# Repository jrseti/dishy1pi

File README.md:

# dishy1pi
Satellite dish motor control for Raspberry Pi, hardware and software

This project was developed in Windows 11 with Python 3.12.

## Prerequisites

It is suggested to create a Python3 virtual environment for this project. Here is how:

- From the project root directory "python3 -m venv .venv"
- .\.venv\Scripts\activate (Note: this command will be a bit different on Linux or MacOS)

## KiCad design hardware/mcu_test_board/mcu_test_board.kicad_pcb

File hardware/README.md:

# Hardware Projects for Dishy1Pi

This directory contains hardware projects and designs related to the Dishy1Pi, a Raspberry Pi Hat tocontrol motors and encoders for a satellite dish.

## Projects

- **Dishy1Pi**: The main project, a Raspberry Pi Hat designed to control motors and encoders for a satellite dish. It includes schematics, PCB layouts, and bill of materials (BOM).

- **power-supply**: A project focused on designing a power supply unit for the Dishy1Pi, ensuring it can provide the necessary voltage and current for operation.

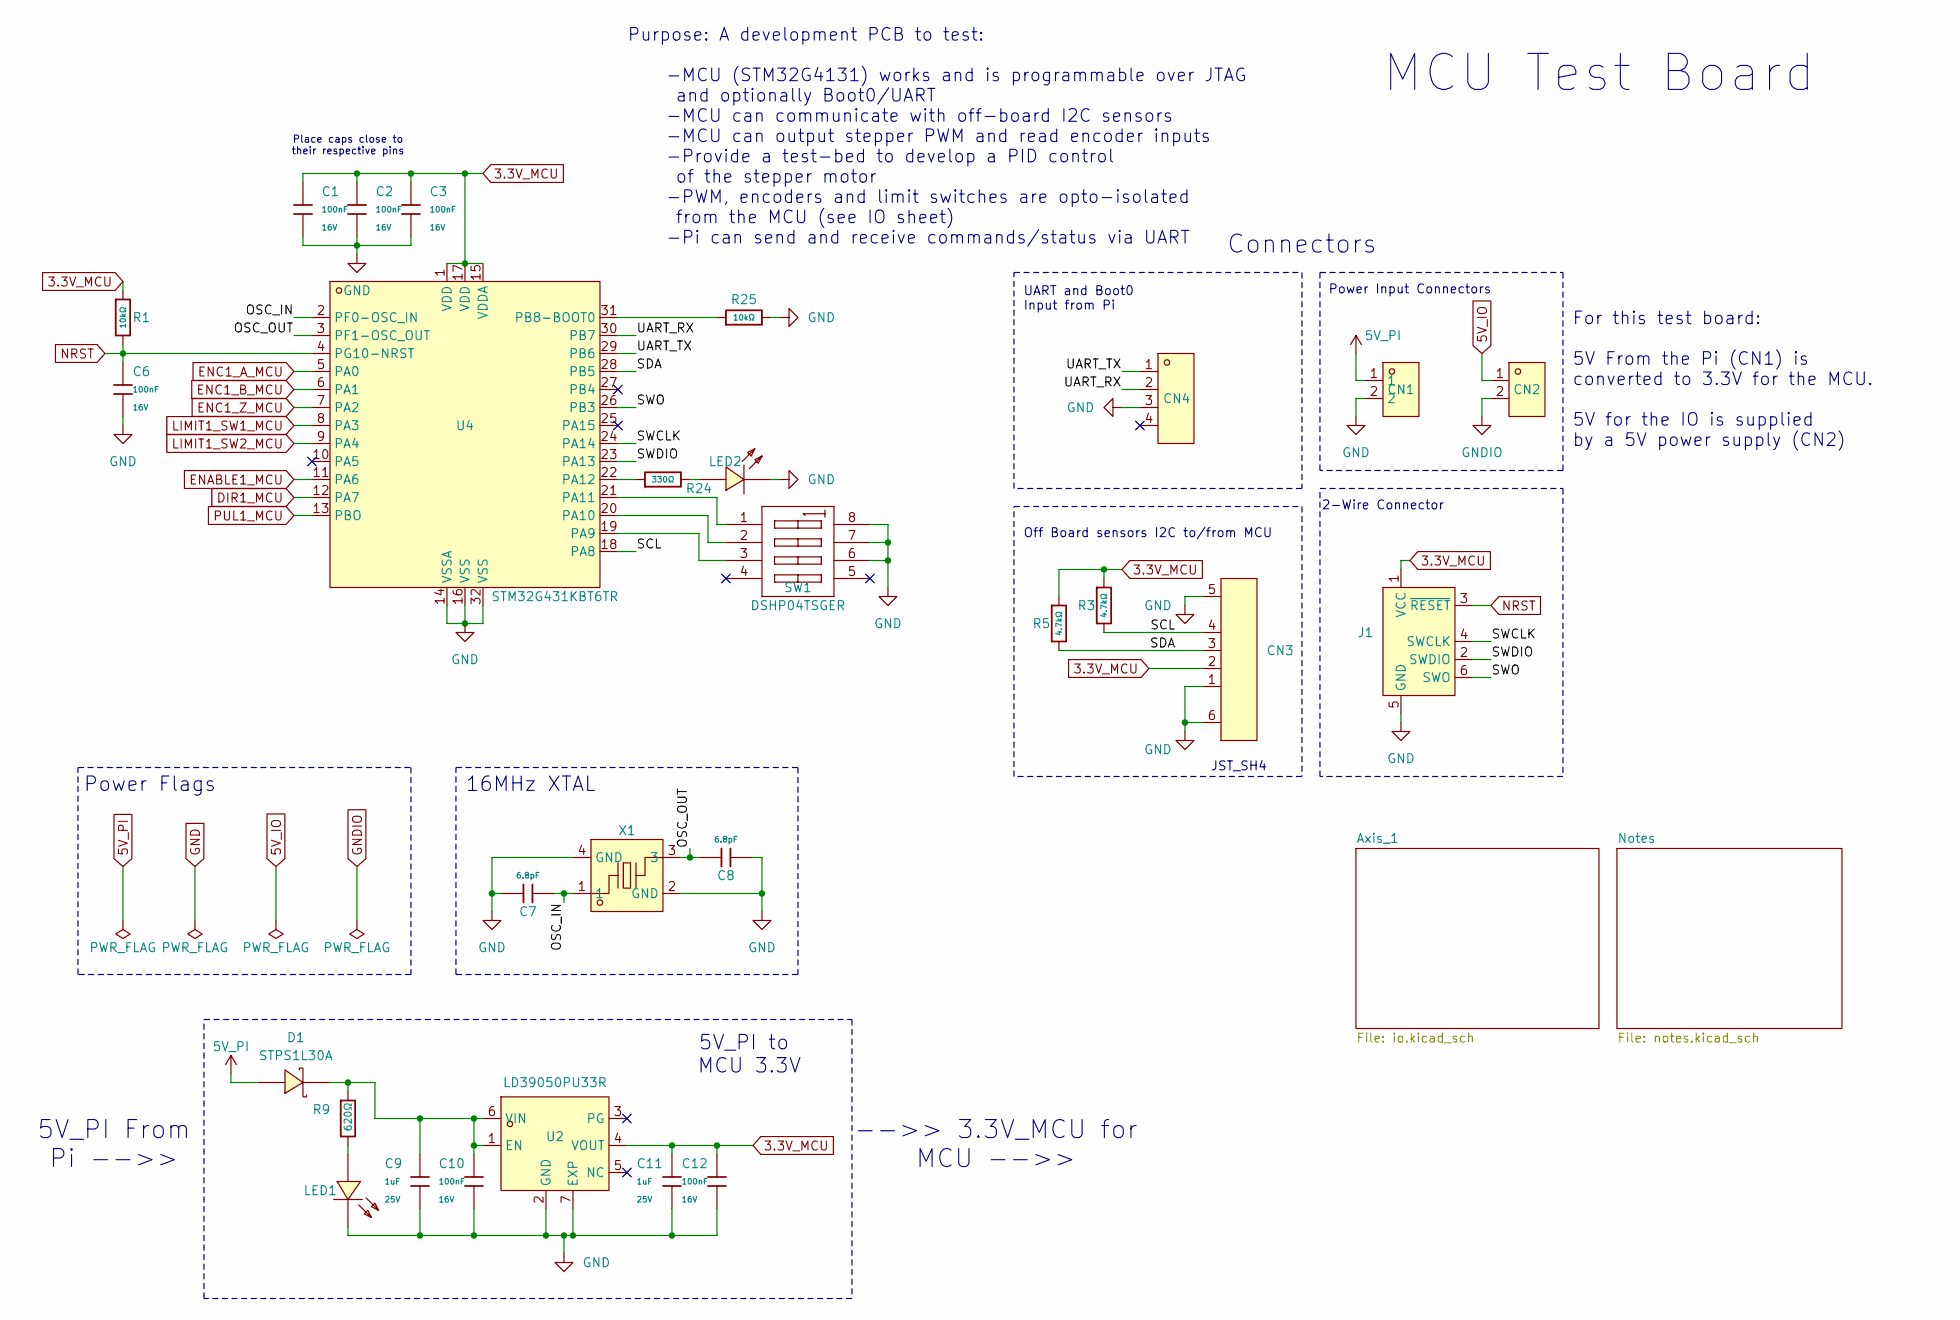
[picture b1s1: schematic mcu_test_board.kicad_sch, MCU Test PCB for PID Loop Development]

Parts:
C1, C2, C3, C6, C10, C12: 100nF; C_0402; Voltage Rated 16V; Tolerance ±10%; Part CL05B104KO5NNNC; LCSC C1525
C7, C8: 6.8pF; C_0402; Voltage Rated 50V; Part 0402CG6R8C500NT; LCSC C1576
C9, C11: 1uF; C_0402; Voltage Rated 25V; Tolerance ±10%; Part CL05A105KA5NQNC; LCSC C52923
CN1, CN2: KF2EDGR-2.54-2P; CONN-TH_P2.54_KF2EDGR-2.54-2P; LCSC Part C577594
CN3: SM04B-SRSS-TB (LF)(SN); CONN-SMD_4P-P1.00_SM04B-SRSS-TB-LF-SN; LCSC Part C160404
CN4: KF2EDGR-2.54-4P; CONN-TH_4P-P2.54_KF2EDGR-2.54-4P; LCSC Part C577596
D1: STPS1L30A; SMA_L4.3-W2.6-LS5.2-RD; LCSC Part C157388
J1: Conn_ARM_SWD_TagConnect_TC2030-NL; Tag-Connect_TC2030-IDC-NL_2x03_P1.27mm_Vertical
LED1, LED2: 19-213SYGC/S530-E2/TR8; LED-SMD_L1.6-W0.8-FD_GREEN; LCSC Part C409444
R1, R25: 10kΩ; R_0402; Overload Voltage (Max) 50V; Tolerance ±1%; Part 0402WGF1002TCE; LCSC C25744
R3, R5: 4.7kΩ; R_0402; Overload Voltage (Max) 50V; Tolerance ±1%; Part 0402WGF4701TCE; LCSC C25900
R9: 620Ω; R_0603; Overload Voltage (Max) 75V; Tolerance ±1%; Part 0603WAF6200T5E; LCSC C23220
R24: 330Ω; R_0402; Overload Voltage (Max) 50V; Tolerance ±1%; Part 0402WGF3300TCE; LCSC C25104
SW1: DSHP04TSGER; SW-SMD_8P-L6.7-W5.4-P1.27-LS8.4; LCSC Part C40736
U2: LD39050PU33R; DFN-6_L3.0-W3.0-P0.95-LS3.1-TL-EP; LCSC Part C132827
U4: STM32G431KBT6TR; LQFP-32_L7.0-W7.0-P0.80-LS9.0-BL; LCSC Part C5270317
X1: NX2016SA-16MHZ-EXS00A-CS07826; CRYSTAL-SMD_4P-L2.0-W1.6-BL; LCSC Part C7322371

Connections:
3.3V_MCU: C1.1, C2.1, C3.1, C11.1, C12.1, CN3.2, J1.1 (VCC), R1.1, R3.1, R5.1, U2.4 (VOUT), U4.1 (VDD), U4.15 (VDDA), U4.17 (VDD); also elsewhere on the board
5V_IO: CN2.1; also elsewhere on the board
5V_PI: CN1.1, D1.2 (A)
/OSC_IN: C7.2, U4.2 (PF0-OSC_IN), X1.1
/OSC_OUT: C8.1, U4.3 (PF1-OSC_OUT), X1.3
/SCL: CN3.4, R3.2, U4.18 (PA8)
/SDA: CN3.3, R5.2, U4.28 (PB5)
/SWCLK: J1.4 (SWCLK), U4.24 (PA14)
/SWDIO: J1.2 (SWDIO), U4.23 (PA13)
/SWO: J1.6 (SWO), U4.26 (PB3)
/UART_RX: CN4.2, U4.30 (PB7)
/UART_TX: CN4.1, U4.29 (PB6)
DIR1_MCU: U4.12 (PA7); also elsewhere on the board
ENABLE1_MCU: U4.11 (PA6); also elsewhere on the board
ENC1_A_MCU: U4.5 (PA0); also elsewhere on the board
ENC1_B_MCU: U4.6 (PA1); also elsewhere on the board
ENC1_Z_MCU: U4.7 (PA2); also elsewhere on the board
GND: C1.2, C2.2, C3.2, C6.2, C7.1, C8.2, C9.2, C10.2, C11.2, C12.2, CN1.2, CN3.1, CN3.5, CN3.6, CN4.3, J1.5 (GND), LED1.2 (-), LED2.2 (-), R25.2, SW1.6 (B3), SW1.7 (B2), SW1.8 (B1), U2.2 (GND), U2.7 (EXP), U4.14 (VSSA), U4.16 (VSS), U4.32 (VSS), X1.2 (GND), X1.4 (GND); also elsewhere on the board
GNDIO: CN2.2; also elsewhere on the board
LIMIT1_SW1_MCU: U4.8 (PA3); also elsewhere on the board
LIMIT1_SW2_MCU: U4.9 (PA4); also elsewhere on the board
NRST: C6.1, J1.3 (~RESET), R1.2, U4.4 (PG10-NRST)
unnamed: C9.1, C10.1, D1.1 (C), R9.1, U2.1 (EN), U2.6 (VIN)
unnamed: LED1.1 (+), R9.2
unnamed: LED2.1 (+), R24.2
unnamed: SW1.1 (A1), U4.21 (PA11)
unnamed: SW1.2 (A2), U4.20 (PA10)
unnamed: SW1.3 (A3), U4.19 (PA9)
unnamed: R24.1, U4.22 (PA12)
unnamed: R25.1, U4.31 (PB8-BOOT0)
PUL1_MCU: U4.13 (PBO); also elsewhere on the board

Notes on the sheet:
2-Wire Connector
16MHz XTAL
Off Board sensors I2C to/from MCU
Connectors
JST_SH4
Power Input Connectors
UART and Boot0 Input from Pi
For this test board: 5V From the Pi (CN1) is converted to 3.3V for the MCU. 5V for the IO is supplied by a 5V power supply (CN2)
Place caps close to their respective pins
Power Flags
-->> 3.3V_MCU for MCU -->>
MCU Test Board
Purpose: A development PCB to test: -MCU (STM32G4131) works and is programmable over JTAG and optionally Boot0/UART -MCU can communicate with off-board I2C sensors -MCU can output stepper PWM and read encoder inputs -Provide a test-bed to develop a PID control of the stepper motor -PWM, encoders an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
5V_PI to MCU 3.3V
5V_PI From Pi -->>

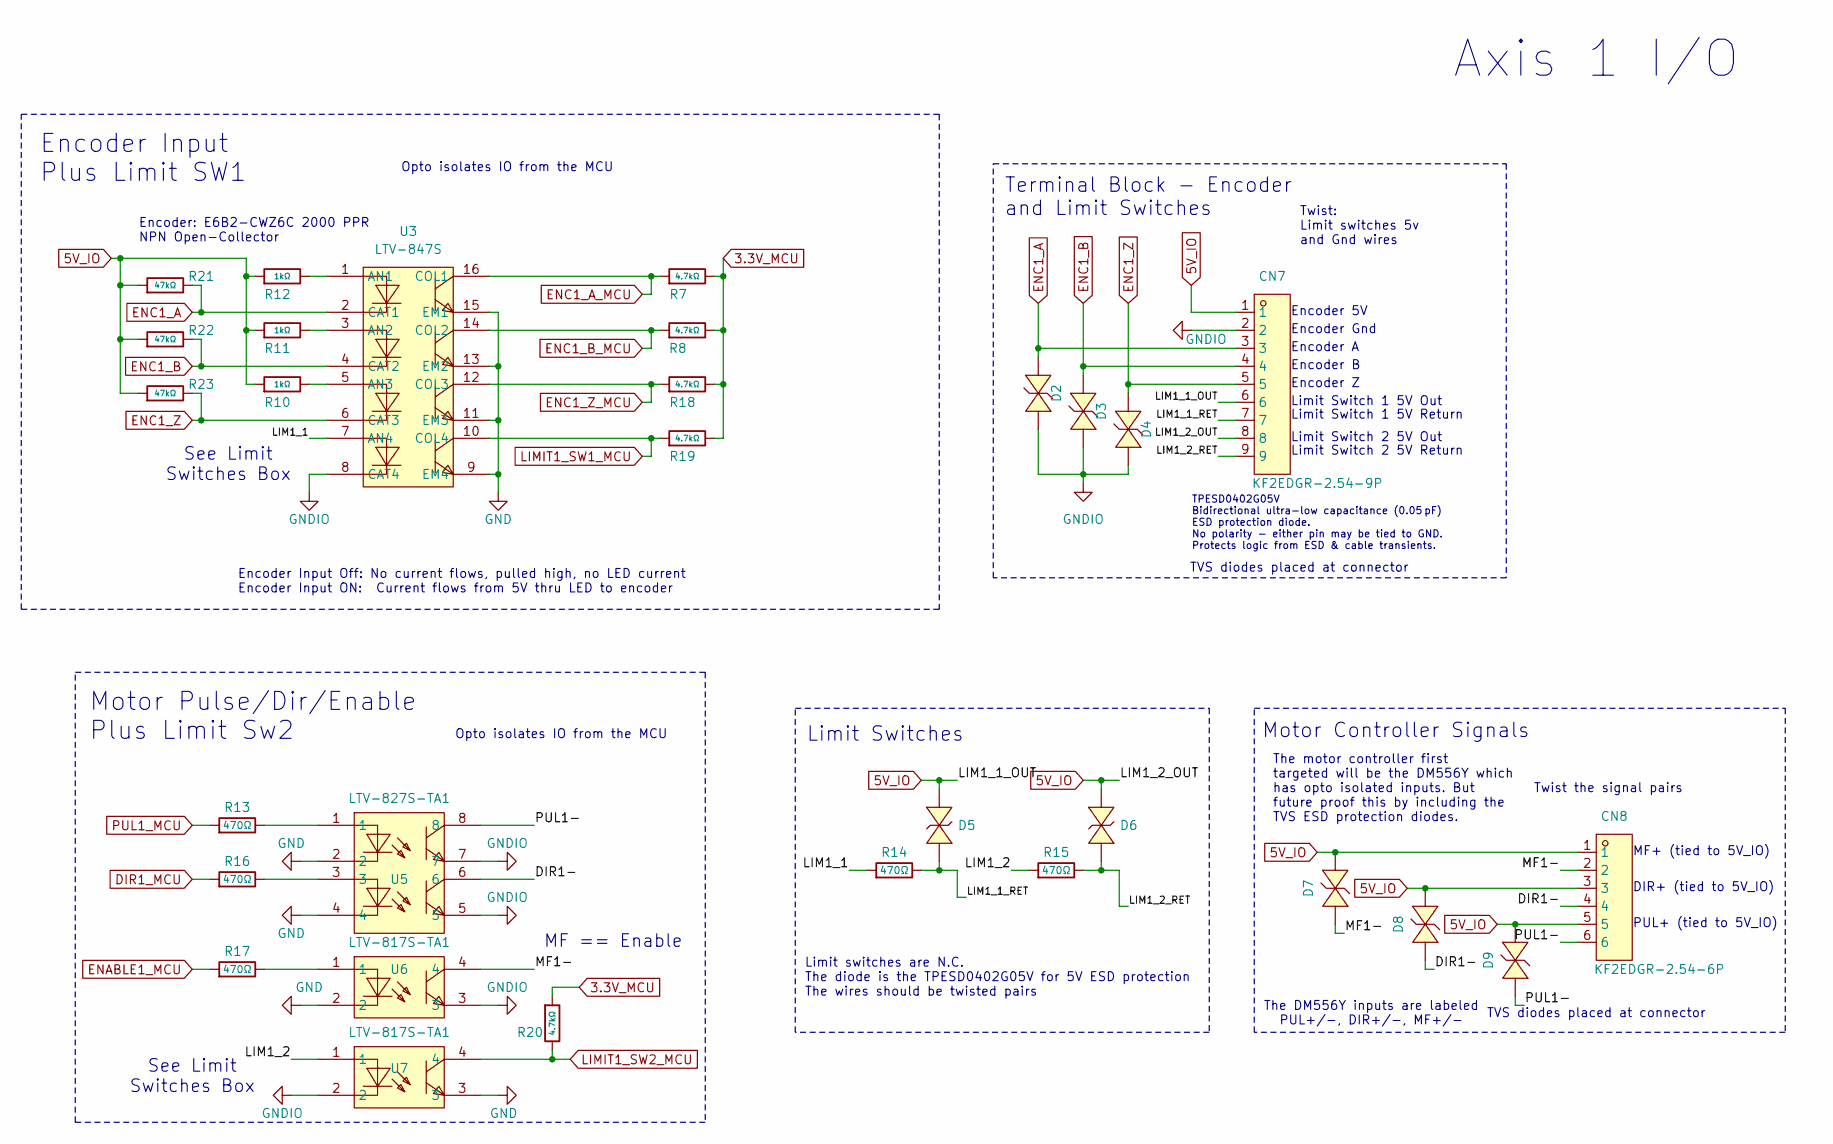
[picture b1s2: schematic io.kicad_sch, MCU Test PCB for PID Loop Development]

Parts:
CN7: KF2EDGR-2.54-9P; CONN-TH_9P-P2.54_KF2EDGR-2.54-9P; LCSC Part C577601
CN8: KF2EDGR-2.54-6P; CONN-TH_KF2EDGR-2.54-6P; LCSC Part C577598
D2, D3, D4, D7, D8, D9: TPESD0402G05V; D0402-BI; LCSC Part C558615
D5, D6: TPESD0402G05V; D0402-BI; LCSC Part C558617
R7, R8, R18, R19, R20: 4.7kΩ; R_0603; Overload Voltage (Max) 75V; Tolerance ±1%; Part 0603WAF4701T5E; LCSC C23162
R10, R11, R12: 1kΩ; R_0402; Overload Voltage (Max) 50V; Tolerance ±1%; Part 0402WGF1001TCE; LCSC C11702
R13, R14, R15, R16, R17: 470Ω; R_0402; Overload Voltage (Max) 50V; Tolerance ±1%; Part 0402WGF4700TCE; LCSC C25117
R21, R22, R23: 47kΩ; R_0402; Overload Voltage (Max) 50V; Tolerance ±1%; Part 0402WGF4702TCE; LCSC C25792
U3: LTV-847S; SMD-16_L20.0-W6.5-P2.54-LS10.2-BL; LCSC Part C114599
U5: LTV-827S-TA1; LTV827S-TA1; LCSC Part C22112
U6, U7: LTV-817S-TA1; LTV817S; LCSC Part C125121

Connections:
3.3V_MCU: R7.2, R8.2, R18.2, R19.2, R20.1; also elsewhere on the board
5V_IO: CN7.1, CN7.6, CN7.8, CN8.1, CN8.3, CN8.5, D5.1, D6.1, D7.1 (K), D8.1 (K), D9.1 (K), R10.1, R11.1, R12.1, R21.1, R22.1, R23.1; also elsewhere on the board
/Axis_1/DIR1-: CN8.4, D8.2 (A), U5.6
/Axis_1/LIM1_1: R14.1, U3.7 (AN4)
/Axis_1/LIM1_1_RET: CN7.7, D5.2, R14.2
/Axis_1/LIM1_2: R15.1, U7.1
/Axis_1/LIM1_2_RET: CN7.9, D6.2, R15.2
/Axis_1/MF1-: CN8.2, D7.2 (A), U6.4
/Axis_1/PUL1-: CN8.6, D9.2 (A), U5.8
DIR1_MCU: R16.1; also elsewhere on the board
ENABLE1_MCU: R17.1; also elsewhere on the board
ENC1_A: CN7.3, D2.1 (K), R21.2, U3.2 (CAT1)
ENC1_A_MCU: R7.1, U3.16 (COL1); also elsewhere on the board
ENC1_B: CN7.4, D3.1 (K), R22.2, U3.4 (CAT2)
ENC1_B_MCU: R8.1, U3.14 (COL2); also elsewhere on the board
ENC1_Z: CN7.5, D4.1 (K), R23.2, U3.6 (CAT3)
ENC1_Z_MCU: R18.1, U3.12 (COL3); also elsewhere on the board
GND: U3.9 (EM4), U3.11 (EM3), U3.13 (EM2), U3.15 (EM1), U5.2, U5.4, U6.2, U7.3; also elsewhere on the board
GNDIO: CN7.2, D2.2 (A), D3.2 (A), D4.2 (A), U3.8 (CAT4), U5.5, U5.7, U6.3, U7.2; also elsewhere on the board
LIMIT1_SW1_MCU: R19.1, U3.10 (COL4); also elsewhere on the board
LIMIT1_SW2_MCU: R20.2, U7.4; also elsewhere on the board
unnamed: R13.2, U5.1
unnamed: R16.2, U5.3
unnamed: R17.2, U6.1
unnamed: R12.2, U3.1 (AN1)
unnamed: R11.2, U3.3 (AN2)
unnamed: R10.2, U3.5 (AN3)
PUL1_MCU: R13.1; also elsewhere on the board

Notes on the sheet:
Limit Switch 2 5V Return
Encoder A
Limit switches are N.C. The diode is the TPESD0402G05V for 5V ESD protection The wires should be twisted pairs
PUL+ (tied to 5V_IO)
Opto isolates IO from the MCU
Encoder 5V
Motor Pulse/Dir/Enable Plus Limit Sw2
See Limit Switches Box
Encoder: E6B2-CWZ6C 2000 PPR NPN Open-Collector
Opto isolates IO from the MCU
Encoder Gnd
Axis 1 I/O
Twist: Limit switches 5v and Gnd wires
TPESD0402G05V Bidirectional ultra-low capacitance (0.05 pF) ESD protection diode. No polarity - either pin may be tied to GND. Protects logic from ESD & cable transients.
Limit Switch 2 5V Out
Encoder Input Off: No current flows, pulled high, no LED current Encoder Input ON: Current flows from 5V thru LED to encoder
TVS diodes placed at connector
MF+ (tied to 5V_IO)
Limit Switch 1 5V Return
Terminal Block - Encoder and Limit Switches
The DM556Y inputs are labeled PUL+/-, DIR+/-, MF+/-
Encoder Input Plus Limit SW1
Limit Switches
Motor Controller Signals
Encoder Z
DIR+ (tied to 5V_IO)
The motor controller first targeted will be the DM556Y which has opto isolated inputs. But future proof this by including the TVS ESD protection diodes.
Twist the signal pairs
MF == Enable
Limit Switch 1 5V Out
Encoder B

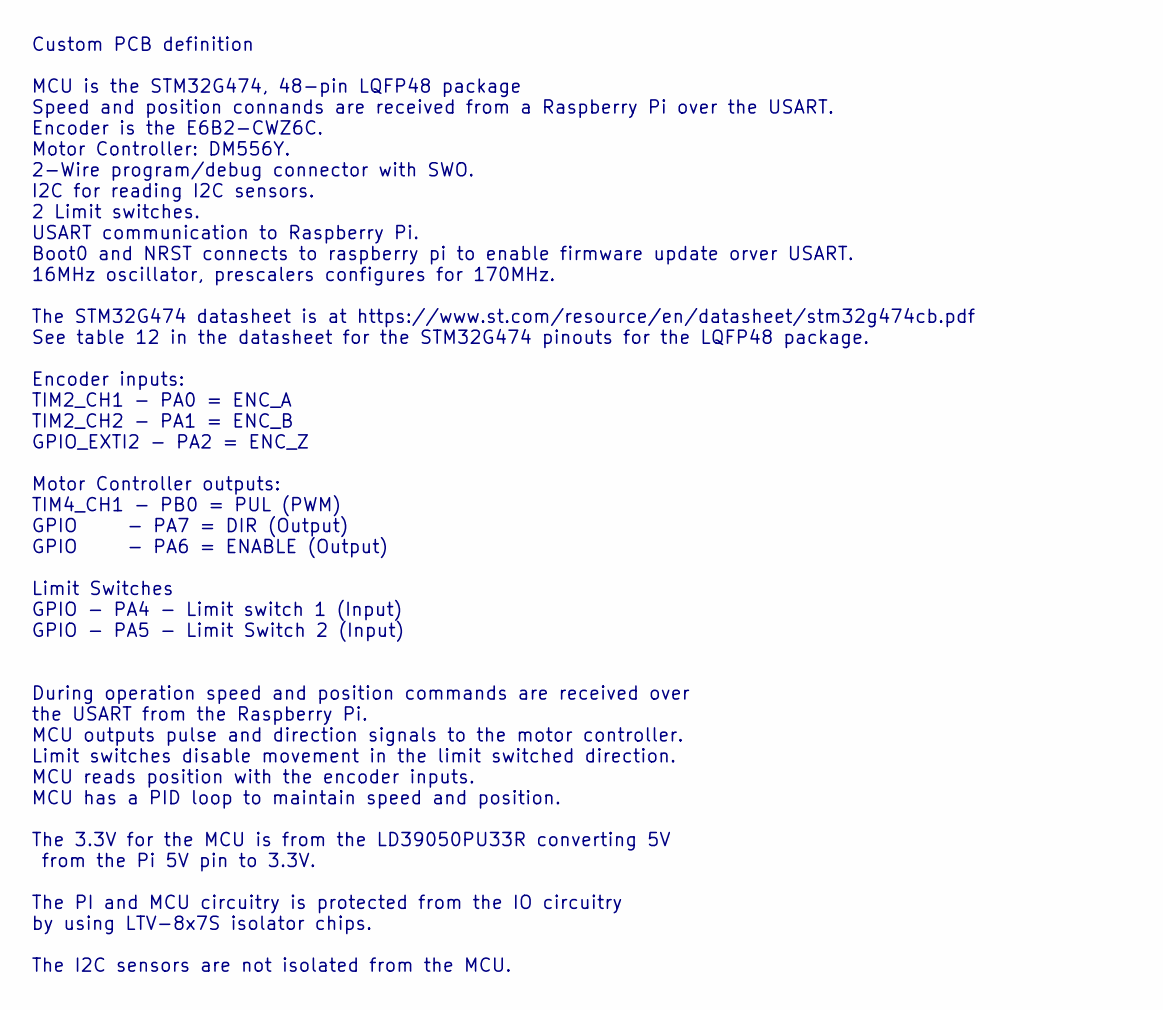
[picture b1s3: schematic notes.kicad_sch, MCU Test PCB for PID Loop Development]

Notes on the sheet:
Custom PCB definition MCU is the STM32G474, 48-pin LQFP48 package Speed and position connands are received from a Raspberry Pi over the USART. Encoder is the E6B2-CWZ6C. Motor Controller: DM556Y. 2-Wire program/debug connector with SWO. I2C for reading I2C sensors. 2 Limit switches. USART communica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

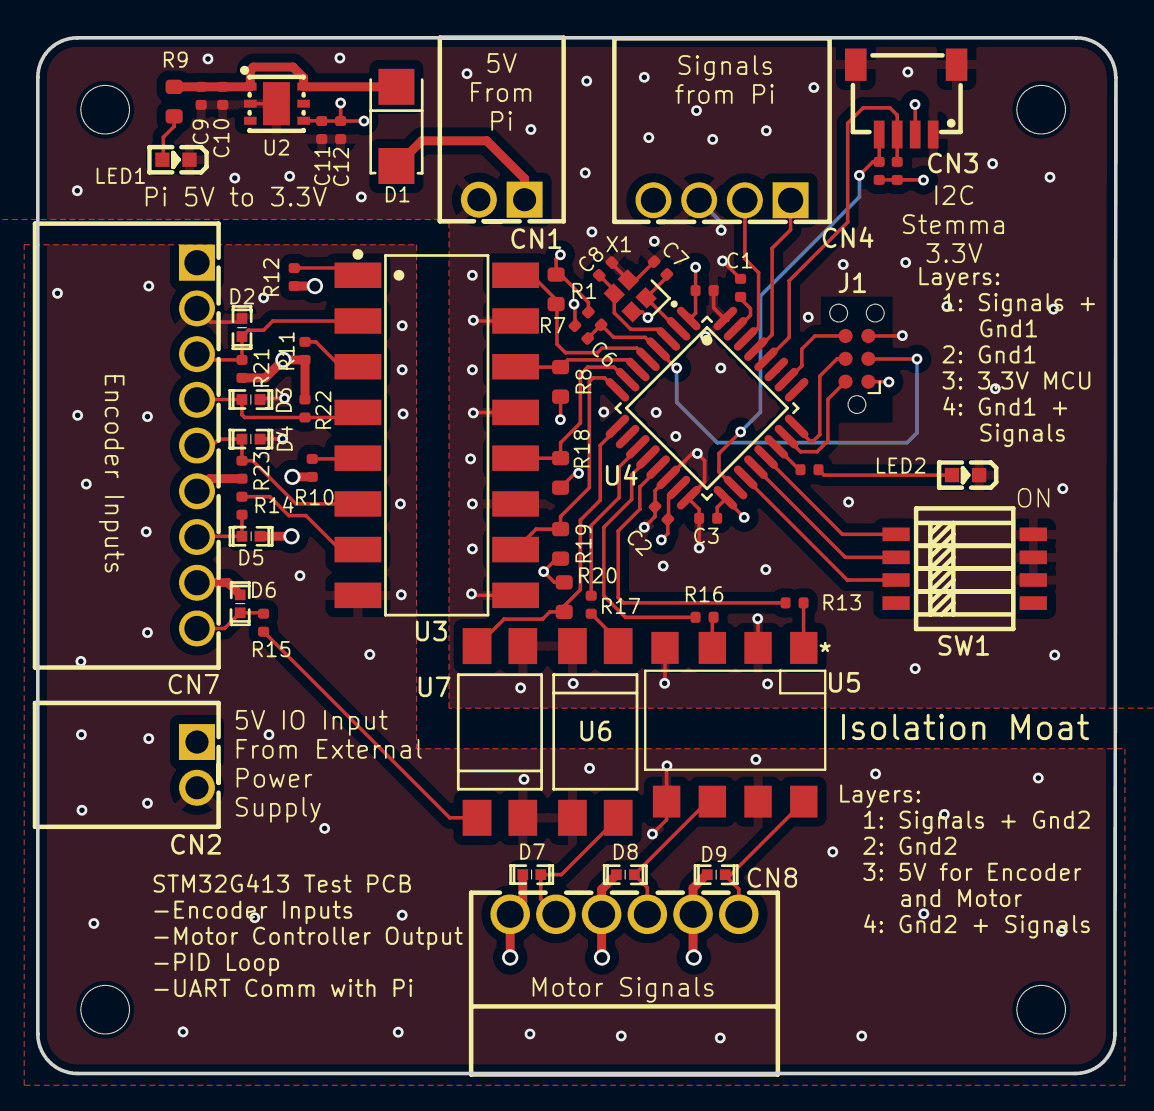
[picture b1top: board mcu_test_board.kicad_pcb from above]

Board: 4 copper layers, 59.9 x 57.5 mm, 62 parts (0 on the bottom side), 47 nets.

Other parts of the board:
M1, M1#2, M1#3, M1#4: MountingHole_2.7mm_M2.5_ISO14580

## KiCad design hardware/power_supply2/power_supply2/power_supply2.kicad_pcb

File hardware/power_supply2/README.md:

# Power Supply circuit based on the MP2322 Buck Chip
This is a simple PCB to test creating several voltages that are used on the Dishy1Pi PCB. Once this cirction is tested as working, the relevant schematic parts will be moved over to the DishyPi1 schematic. The voltages needed are:
- 12V to power each of the 2 encoders. This voltage is supplied from an external power supply and protected by a PTC fuse on the Dishy1Pi PCB. Also reverse polatiry protected.
- 5V to power the logic circuity on the Dishy1Pi PCB.

The buck chip is the MP2322 from Monolithic Power Systems. Link to datasheet: https://www.monolithicpower.com/en/documentview/productdocument/index/version/1/document_type/Datasheet/lang/en/sku/MP2322

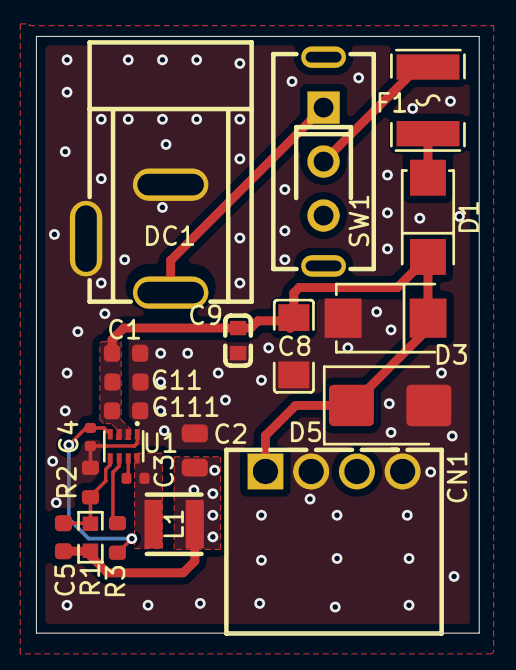
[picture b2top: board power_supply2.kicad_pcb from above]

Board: 4 copper layers, 24.6 x 33.1 mm, 21 parts (0 on the bottom side), 11 nets.

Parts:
C1: 100nF; C_0603
C2: 22uF; C_0805
C3: 22pF; C_0402
C4: 1uF; C_0402
C5: 22pF; C_0603
C8: 47uF; C1206
C9: 100nF; C0603
C11, C111: 10uF; C_0603
CN1: KF2EDGR-2.54-4P; CONN-TH_4P-P2.54_KF2EDGR-2.54-4P
D1: SS34; SMA_L4.3-W2.6-LS5.2-RD
D3: SMBJ18A; SMB_L4.6-W3.6-LS5.3-RD
D5: SMBJ16A; D_SMB
DC1: DC-005-2.5A-2.0; CONN-TH_DC-005-2.5A-2.0
F1: 1812L110/33MR; F1812
L1: 4.7uH; IND-SMD_L3.0-W3.0-1
R1: 1.62K; R0603
R2: 220Ω; R_0603
R3: 200kΩ; R_0603
SW1: SS-12F49-G050; SW-TH_SS-12F45-GXXX
U1: MP2322GQH-Z; QFN-8_L2.0-W1.5-P0.50-BL

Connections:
/5V: C2.1, C5.1, CN1.3, L1.2, R1.1
/12V_IN: DC1.1, SW1.1
/12V_PROT: C1.1, C8.1, C9.1, C11.1, C111.1, CN1.1, D1.1 (K), D3.1 (K), D5.1, U1.2 (IN), U1.3 (EN)
GND: C1.2, C2.2, C4.2, C8.2, C9.2, C11.2, C111.2, CN1.2, CN1.4, D3.2 (A), D5.2, DC1.2, DC1.3, R2.2, U1.1 (GND)
unnamed: D1.2 (A), F1.2
unnamed: F1.1, SW1.2
unnamed: C3.1, U1.7 (BST)
unnamed: C5.2, R1.2, R2.1, U1.5 (FB)
unnamed: R3.1, U1.6 (PG)
unnamed: C3.2, L1.1, U1.8 (SW)
unnamed: C4.1, R3.2, U1.4 (VCC)

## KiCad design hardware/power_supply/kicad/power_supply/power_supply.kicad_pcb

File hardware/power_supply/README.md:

# Power Supply

This directory contains the design files and documentation for the power supply unit used in the Dishy1Pi project. The power supply is responsible for providing the necessary voltage and current to the Dishy1Pi Hat and its connected components.

Reason for this project:
- The Dishy1Pi Hat requires a stable 5V power supply to operate correctly.
- The power supply to the dish1pi is important to ensure reliable operation.
- There are so many choices for power supplies, I wanted to design my own so I am confident the power supply meets the requirements of the Dishy1Pi Hat.
- I need to learn how to design a power supply for a PCB board.

Project Goals:
- Design a power supply PCB that can take an input voltage range of 12-24VDC
- Output a stable 5VDC at up to 1A
- Create a schematic and PCB layout for the power supply that can be manufactured by JLCPCB.
- Get a board manufactureed and assembled by JLCPCB and test it, verify it works.
- Move the design of the power circuit to the dishy1pi project.

KiCad will be used for this project.

Used TI's WEBENCH Power Designer to design the power supply around the TPS62932 buck converter IC. Link: https://webench.ti.com/power-designer/

Out of the myriad of chioces I selected to use the TPS62932DRLR. See the full report, in PDF, created by WEBENCH. Power Supply Report: [power_supply_report.pdf](docs/PowerSupplyDesignReport.pdf)

The WEBENCH report (see PDF) included a BOM. Equivalent components available from LCSC have been identified. LCSC components were identified with properties that match as close as possible to the original BOM.

| Name  | Manufacturer     | Part Number              | Properties                                                                 | Qty | Footprint      | LCSC | Notes |
|-------|------------------|--------------------------|----------------------------------------------------------------------------|-----|----------------|------|-------|
| Cboot(C1) | MuRata           | GRM155R71A104KA01D       | Series=X7R;<br>Cap=100.0 nF<br>ESR=1.0 mΩ;<br>VDC=10.0 V;<br>IRMS=0.0 A   | 1   | 0402 3 mm²     |  C71687    |       |
| Cff(C2)   | TDK              | CGA1A2C0G1E180J030BA     | Series=C0G/NP0;<br>Cap=18.0 pF;<br>VDC=25.0 V;<br>IRMS=0.0 A              | 1   | 0201 2 mm²     | C599585    |   C0402C180J5GAC7867, 0402    |
| Cin(C3)   | Taiyo Yuden      | MSASU32MSB5106KPNA01     | Series=X5R;<br>Cap=10.0 µF;<br>ESR=3.979 mΩ;<br>VDC=50.0 V;<br>IRMS=3.4821 A | 1   | 1210 15 mm²    |  C5677734    |       |
| Cinx(C4)  | TDK              | CGA3E2X7R1H104K080AA     | Series=X7R;<br>Cap=100.0 nF;<br>ESR=29.6 mΩ;<br>VDC=50.0 V;<br>IRMS=971.99 mA | 1   | 0603 5 mm²     |  C14663  |  CC0603KRX7R9BB104     |
| Cout  | MuRata           | GRM32ER61C476KE15L       | Series=X5R;<br>Cap=47.0 µF;<br>ESR=3.037 mΩ;<br>VDC=16.0 V;<br>IRMS=4.59346 A | 1   | 1210_280 15 mm²| C5440143   |   CS3225X7R476K160NRL    |
| Css   | MuRata           | GRM155R71A333KA01D       | Series=X7R;<br>Cap=33.0 nF;<br>ESR=1.0 mΩ;<br>VDC=10.0 V;<br>IRMS=0.0 A   | 1   | 0402 3 mm²     |     C307488  |  CL10B333KB8NFNC, 0603     |
| L1    | Bourns           | SRR1208-100ML            | L=10.0 µH; DCR=21.0 mΩ                                                     | 1   | SRR1208 216 mm²|   C2041331  |    STEP@SnapMagic   |
| Rfbb  | Vishay-Dale      | CRCW040210K0FKED         | Series=CRCW..e3; Res=10.0 kΩ; Power=63.0 mW; Tol=1.0%                      | 1   | 0402 3 mm²     |  C71617    |     |
| Rfbt  | Yageo            | RC0603FR-0752K3L         | Res=52.3 kΩ; Power=100.0 mW; Tol=1.0%                                      | 1   | 0603 5 mm²     |   C23198  |    0603WAF5232T5E, NP   |
| U1    | Texas Instruments| TPS62932DRLR             | Switcher IC                                                                | 1   | DRL0008A-MFG 9 mm² | C3032935 |  STEP@ https://www.snapeda.com/   |
| SW1   | C&K              | SS-12F49-G050            | Switch, SPDT                             | 1   | KSC201  | C2876010 |  Added     |
| D1    | BrtLed(Bright LED Elec)       | BL-HZD33-L21-TRB                | White 3.3V LED                                                 | 1   | 1206     | C5264252  |   Added , no CAD, use Generic LED1206   |
| R1    | VO            | SCR0805J560R             | Res=560Ω;                                     | 1   | 0805    | C3017839  |   Added, Generic 0805 resistor    |

The script **parts.bat** will create a library of the parts named **power_parts**.

Note that L1, D1 and R1 do not have symbol anf footprint files in the JLCPCB database. See the Notes column in the BOM table above for instructions on how to create these parts. All them to the power_parts library.

C5290394 (Male)
C5290400 (Female)

C5290400 (through hole PCB)
C5290400

C577594 - 2.54mm through hole pcb
C577526

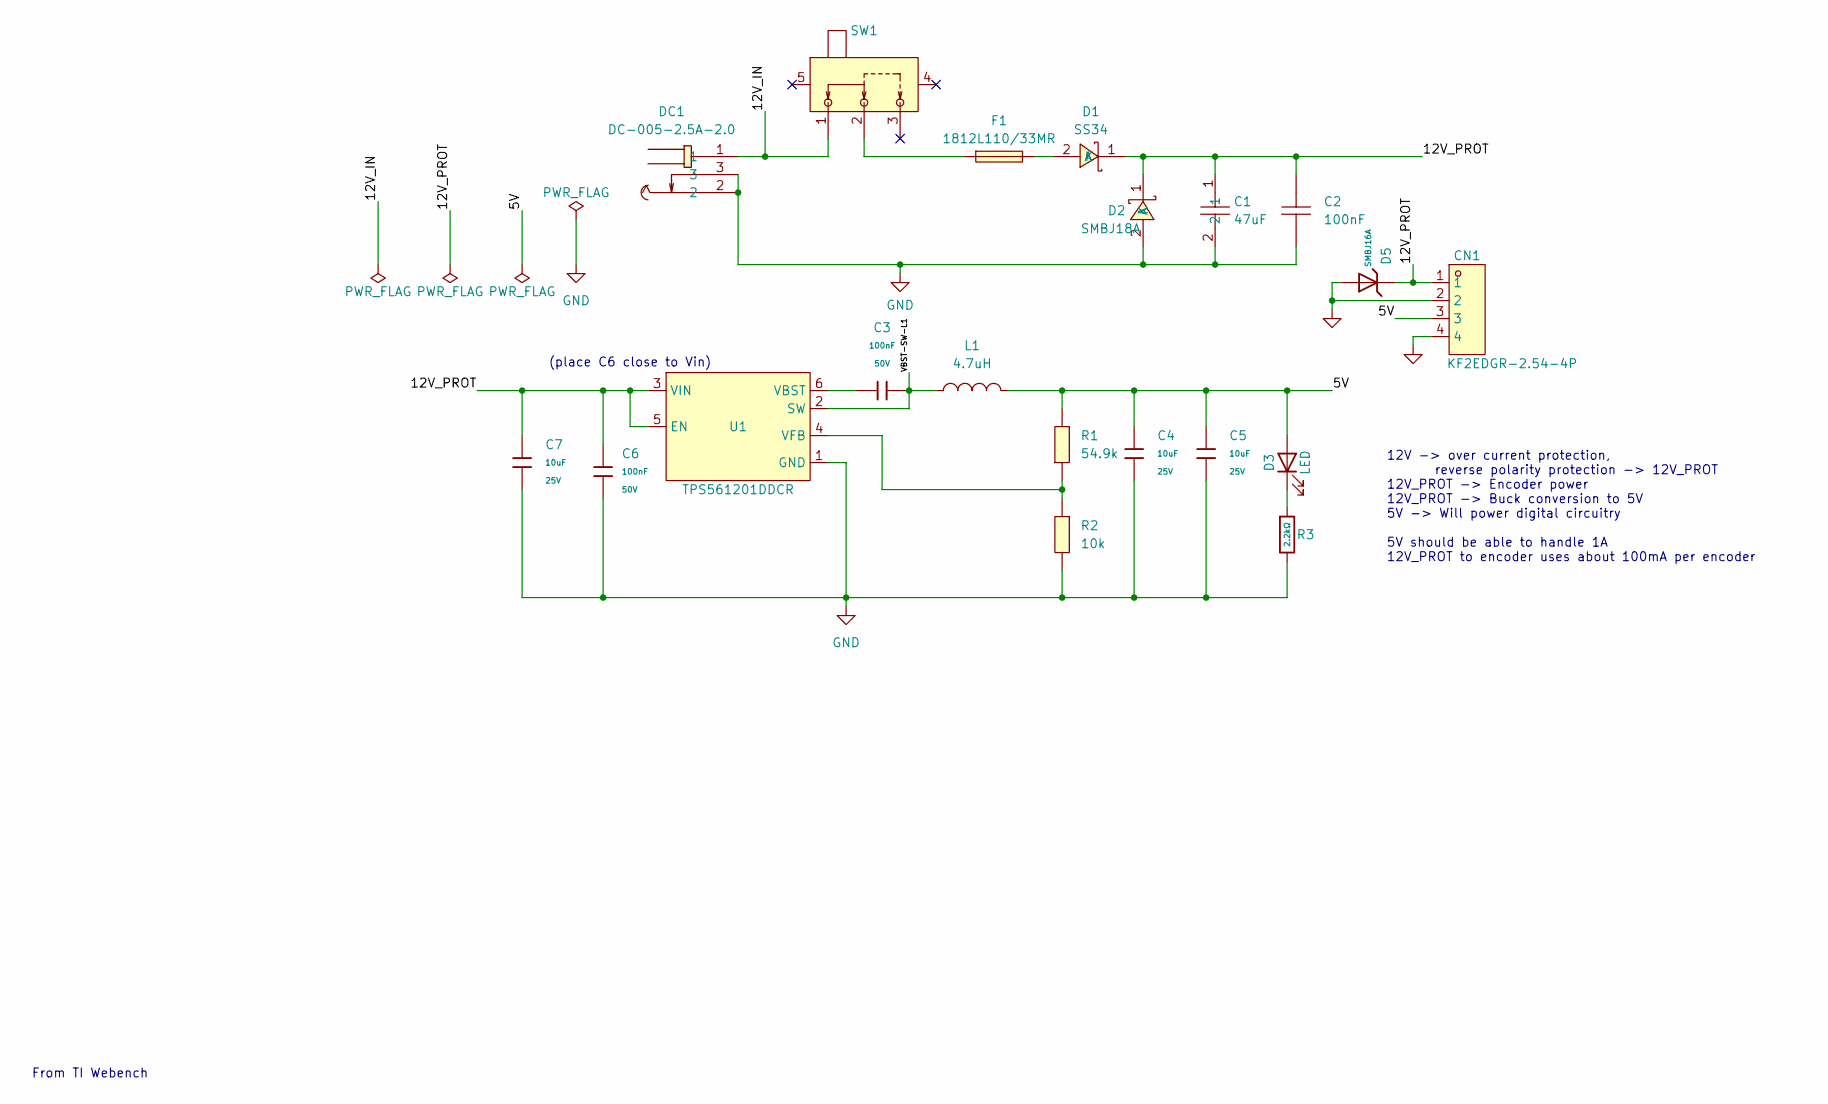
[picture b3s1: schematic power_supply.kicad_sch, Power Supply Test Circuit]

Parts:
C1: 47uF; C1206; LCSC Part C403725
C2: 100nF; C0603; LCSC Part C14663
C3: 100nF; C_0402; Voltage Rated 50V; Tolerance ±10%; Part CL05B104KB54PNC; LCSC C307331
C4, C5, C7: 10uF; C_0805; Voltage Rated 25V; Tolerance ±10%; Part CL21A106KAYNNNE; LCSC C15850
C6: 100nF; C_0805; Voltage Rated 50V; Tolerance ±10%; Part CC0805KRX7R9BB104; LCSC C49678
CN1: KF2EDGR-2.54-4P; CONN-TH_4P-P2.54_KF2EDGR-2.54-4P; LCSC Part C577596
D1: SS34; SMA_L4.3-W2.6-LS5.2-RD; LCSC Part C8678
D2: SMBJ18A; SMB_L4.6-W3.6-LS5.3-RD; LCSC Part C2965323
D3: LED; LED_1206_3216Metric; LCSC Part C5264252
D5: SMBJ16A; D_SMB; Part SMBJ16A; LCSC C19077571
DC1: DC-005-2.5A-2.0; CONN-TH_DC-005-2.5A-2.0; LCSC Part C319099
F1: 1812L110/33MR; F1812; LCSC Part C142747
L1: 4.7uH; IND-SMD_L3.0-W3.0-1; LCSC Part C7427089
R1: 54.9k; R0603; LCSC Part C23077
R2: 10k; R0603; LCSC Part C25804
R3: 2.2kΩ; R_0402; Overload Voltage (Max) 50V; Tolerance ±1%; Part 0402WGF2201TCE; LCSC C25879
SW1: SS-12F49-G050; SW-TH_SS-12F45-GXXX; LCSC Part C2876010
U1: TPS561201DDCR; SOT-23-6_L2.9-W1.6-P0.95-LS2.8-BR; LCSC Part C220433

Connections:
/5V: C4.1, C5.1, CN1.3, D3.2 (A), L1.2, R1.2
/12V_IN: DC1.1, SW1.1
/12V_PROT: C1.1, C2.1, C6.1, C7.1, CN1.1, D1.1 (K), D2.1 (K), D5.1, U1.3 (VIN), U1.5 (EN)
/VBST-SW-L1: C3.2, L1.1, U1.2 (SW)
GND: C1.2, C2.2, C4.2, C5.2, C6.2, C7.2, CN1.2, CN1.4, D2.2 (A), D5.2, DC1.2, DC1.3, R2.2, R3.2, U1.1 (GND)
unnamed: D1.2 (A), F1.2
unnamed: D3.1 (K), R3.1
unnamed: F1.1, SW1.2
unnamed: C3.1, U1.6 (VBST)
unnamed: R1.1, R2.1, U1.4 (VFB)

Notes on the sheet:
From TI Webench
(place C6 close to Vin)
12V -> over current protection, reverse polarity protection -> 12V_PROT 12V_PROT -> Encoder power 12V_PROT -> Buck conversion to 5V 5V -> Will power digital circuitry 5V should be able to handle 1A 12V_PROT to encoder uses about 100mA per encoder

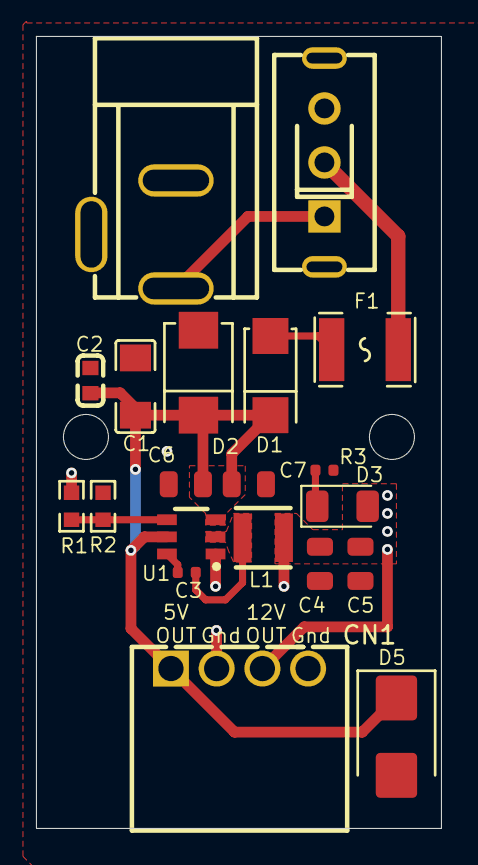
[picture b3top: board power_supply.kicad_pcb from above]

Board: 4 copper layers, 22.5 x 44.0 mm, 20 parts (0 on the bottom side), 10 nets.

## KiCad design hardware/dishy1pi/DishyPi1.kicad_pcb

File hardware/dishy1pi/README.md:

# Dishy1Pi Hardware

The hardware part of the Dishy1Pi project is a Raspberry Pi Hat board which interfaces the Raspberry Pi GPIO pins with the satellite dish motor controllers, encoders, and various sensors. An important aspect of this board is that the Raspberry Pi is optically isolated from the hardware connected to the satellite dish.

Although this project is tailored to controlling a satellite dish, it can also be used for controlling other motor control systems that require isolation and encoder feedback.

## Parts Library

The PCB will be assembled by JCLPCB. The project will require parts number identification to be compatible with LCSC part numbers. See [Library README](libs/README.md)

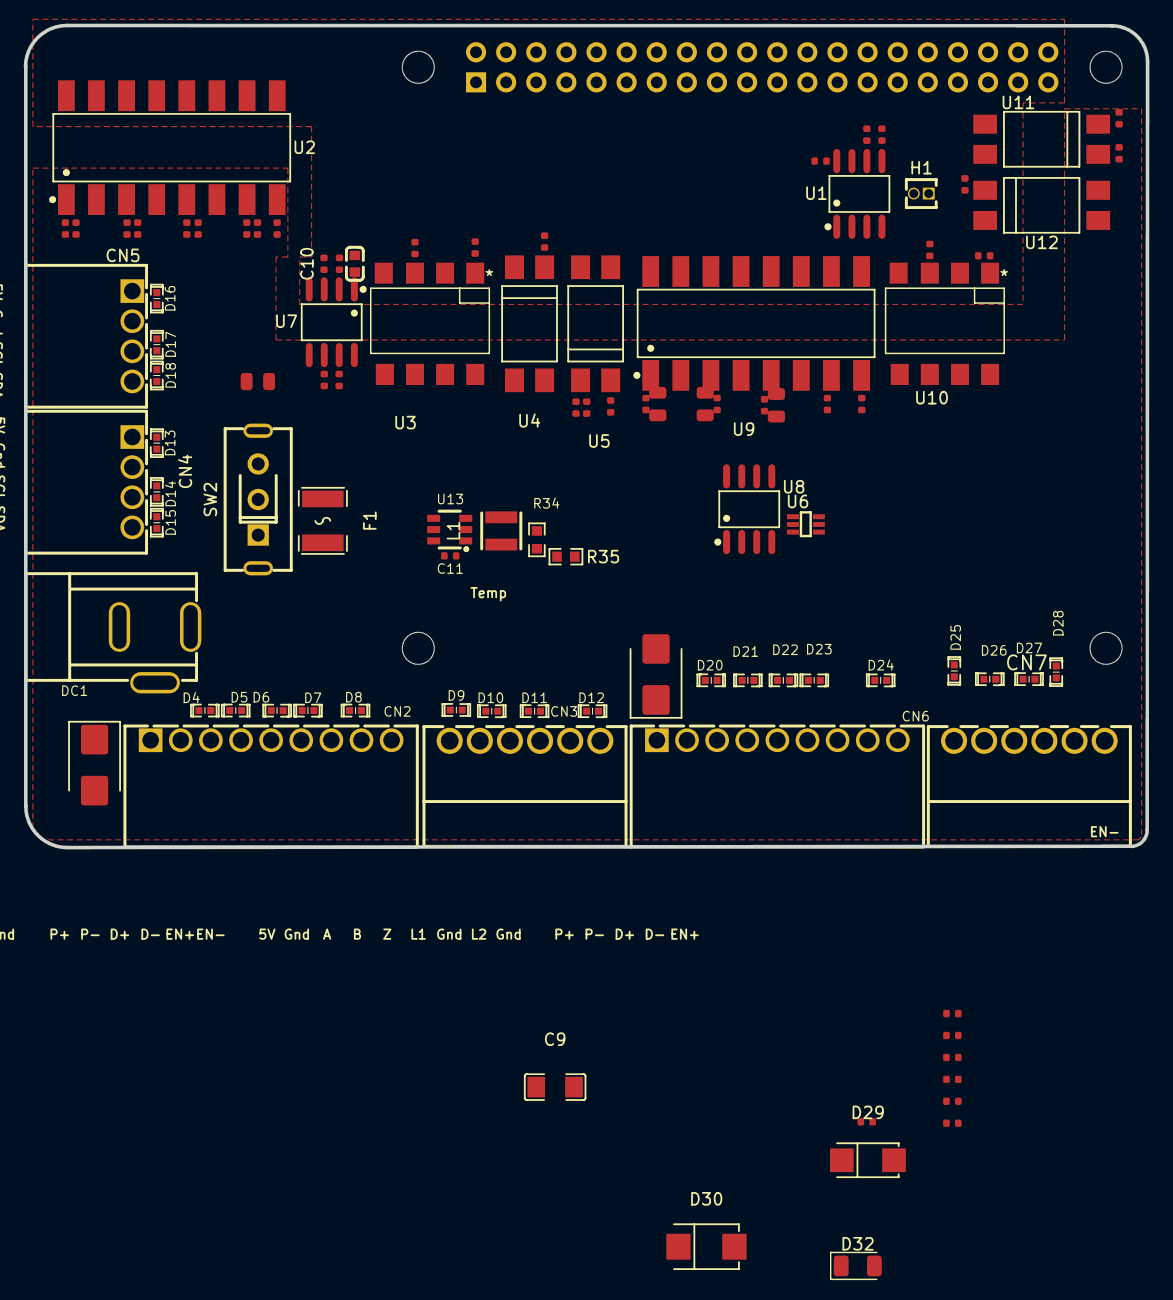
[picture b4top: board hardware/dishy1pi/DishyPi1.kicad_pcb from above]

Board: 4 copper layers, 94.6 x 69.3 mm, 106 parts (1 on the bottom side), 67 nets, no tracks yet.

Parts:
C3, C5, C6, C7, C8, C11: 100nF; C_0402
C4: 100pF; C_0402
C9: 47uF; C1206
C10: 100nF; C0603
C12, C13, C14: 10uF; C_0805
C15: 100nF; C_0805
CN2, CN6: KF2EDGR-2.54-9P; CONN-TH_9P-P2.54_KF2EDGR-2.54-9P
CN3, CN7: KF2EDGR-2.54-6P; CONN-TH_KF2EDGR-2.54-6P
CN4, CN5: KF2EDGR-2.54-4P; CONN-TH_4P-P2.54_KF2EDGR-2.54-4P
D4, D5, D6, D7, D8, D9, D10, D11, D12, D13, D14, D15, D16, D17, D18, D20, D21, D22, D23, D24, D25, D26, D27, D28: TPESD0402G05V; D0402-BI
D29: SS34; SMA_L4.3-W2.6-LS5.2-RD
D30: SMBJ18A_C78412; SMB_L4.6-W3.6-LS5.3-RD
D32: LED; LED_1206_3216Metric
D33, D34: SMBJ16A; D_SMB
DC1: DC-005-2.5A-2.0; CONN-TH_DC-005-2.5A-2.0
F1: 1812L110/33MR; F1812
H1: 1.27MM/1*2P; HDR-TH_2P-P1.27-V-M
J1: Conn_02x20_Odd_Even; PinSocket_2x20_P2.54mm_Vertical
L1: 4.7uH; IND-SMD_L3.0-W3.0-1
MH1, MH2, MH3, MH4: MountingHole_2.7mm_M2.5
R2, R3: 3.9kΩ; R_0402
R4, R6, R8, R12, R13, R14, R21, R23, R25, R29, R30, R31: 1kΩ; R_0402
R5, R7, R9, R22, R24, R26: 10kΩ; R_0402
R10, R27: 220Ω; R_0402
R11, R16, R28, R33: 22kΩ; R_0402
R15, R32: 470Ω; R_0402
R17, R18, R19, R20: 4.7kΩ; R_0402
R34: 54.9k; R0603
R35: 10k; R0603
R36: 2.2kΩ; R_0402
SW2: SS-12F49-G050; SW-TH_SS-12F45-GXXX
U1: CAT24C256WI-GT3; SOIC-8_L4.9-W3.9-P1.27-LS6.0-BL
U2, U9: LTV-847S; SMD-16_L20.0-W6.5-P2.54-LS10.2-BL
U3, U10: LTV-827S-TA1; LTV827S-TA1
U4, U5, U11, U12: LTV-817S-TA1; LTV817S
U6: LTC4311ISC6#TRPBF; SC-70-6_L2.2-W1.3-P0.65-LS2.2-BL
U7: ISO1540DR; SOIC-8_L4.9-W3.9-P1.27-LS6.0-BL
U8: LM75BIMX-5/NOPB; SOIC-8_L4.9-W3.9-P1.27-LS6.0-BL
U13: TPS561201DDCR; SOT-23-6_L2.9-W1.6-P0.95-LS2.8-BR

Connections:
12V_PROT: C9.1, C10.1, C14.1, C15.1, CN2.1, CN6.1, D29.1 (K), D30.1 (K), D33.1, D34.1, U13.3 (VIN), U13.5 (EN)
+3.3V: C3.1, C6.1, H1.1, J1.1, J1.17, R2.1, R3.1, R17.1, R18.1, U1.8 (VCC), U7.1 (VCC1)
+5V: C5.1, C7.1, C8.1, C12.1, C13.1, CN3.1, CN3.3, CN3.5, CN4.1, CN5.1, CN7.1, CN7.3, CN7.5, D9.1 (K), D13.1 (K), D16.2 (A), D25.1 (K), D32.2 (A), L1.2, R4.1, R5.1, R6.1, R7.1, R8.1, R9.1, R10.1, R15.1, R16.2, R19.1, R20.1, R21.1, R22.1, R23.1, R24.1, R25.1, R26.1, R27.1, R28.2, R32.1, R33.2, R34.2, U6.1 (VCC), U6.3 (ENABLE), U7.8 (VCC2), U8.7 (A0), U8.8 (+VS)
/12v_in/12V_IN: DC1.1, SW2.1
/12v_in/VBST-SW-L1: C11.2, L1.1, U13.2 (SW)
/I2C/SCL: CN4.3, CN5.3, D14.1 (K), D17.2 (A), R20.2, U6.4 (BUS2), U7.6 (SCL2), U8.2 (SCL)
/I2C/SDA: CN4.4, CN5.4, D15.1 (K), D18.2 (A), R19.2, U6.6 (BUS1), U7.7 (SDA2), U8.1 (SDA)
/ID_SCL: J1.28, R2.2, U1.6 (SCL)
/ID_SDA: J1.27, R3.2, U1.5 (SDA)
/IO/DIR-: CN3.4, D11.1 (K), U3.8
/IO/ENC_A: CN2.3, D4.1 (K), R9.2, U2.2 (CAT1)
/IO/ENC_B: CN2.4, D5.1 (K), R7.2, U2.4 (CAT2)
/IO/ENC_Z: CN2.5, D6.1 (K), R5.2, U2.6 (CAT3)
/IO/LIM_1: CN2.6, D7.1 (K), R11.1, U2.8 (CAT4)
/IO/LIM_2: CN2.8, D8.1 (K), R16.1, U5.2
/IO/MF-: CN3.6, D12.1 (K), U4.4
/IO/PUL-: CN3.2, D10.1 (K), U3.6
/io2/DIR-: CN7.4, D27.1 (K), U10.6
/io2/ENC_A: CN6.3, D20.1 (K), R26.2, U9.2 (CAT1)
/io2/ENC_B: CN6.4, D21.1 (K), R24.2, U9.4 (CAT2)
/io2/ENC_Z: CN6.5, D22.1 (K), R22.2, U9.6 (CAT3)
/io2/LIM_1: CN6.6, D23.1 (K), R28.1, U9.8 (CAT4)
/io2/LIM_2: CN6.8, D24.1 (K), R33.1, U12.2
/io2/MF-: CN7.6, D28.1 (K), U11.4
/io2/PUL-: CN7.2, D26.1 (K), U10.8
A_DIR/19: J1.35, R30.1
A_ENC_A/5: J1.29, U9.16 (COL1)
A_ENC_B/6: J1.31, U9.14 (COL2)
A_ENC_Z/26: J1.37, U9.12 (COL3)
A_LIM_1/12: J1.32, U9.10 (COL4)
A_LIM_2/21: J1.40, U12.4
A_MF/20: J1.38, R31.1
A_PUL/13: J1.33, R29.1
E_DIR/23: J1.16, R12.1
E_ENC_A/17: J1.11, U2.16 (COL1)
E_ENC_B/22: J1.13, U2.14 (COL2)
E_ENC_Z/27: J1.15, U2.12 (COL3)
E_LIM_1/25: J1.22, U2.10 (COL4)
E_LIM_2/16: J1.36, U5.4
E_MF/24: J1.18, R14.1
E_PUL/18: J1.12, R13.1
GNDIO: C4.2, C5.2, C7.2, C8.2, C9.2, C10.2, C12.2, C13.2, C14.2, C15.2, CN2.2, CN2.7, CN2.9, CN4.2, CN5.2, CN6.2, CN6.7, CN6.9, D4.2 (A), D5.2 (A), D6.2 (A), D7.2 (A), D8.2 (A), D9.2 (A), D10.2 (A), D11.2 (A), D12.2 (A), D13.2 (A), D14.2 (A), D15.2 (A), D16.1 (K), D17.1 (K), D18.1 (K), D20.2 (A), D21.2 (A), D22.2 (A), D23.2 (A), D24.2 (A), D25.2 (A), D26.2 (A), D27.2 (A), D28.2 (A), D30.2 (A), D33.2, D34.2, DC1.2, DC1.3, R11.2, R35.2, R36.2, U3.5, U3.7, U4.3, U6.2 (GND), U6.5 (GND), U7.5 (GND2), U8.4 (GND), U8.5 (A2), U8.6 (A1), U10.5, U10.7, U11.3, U13.1 (GND)
GNDPI: C3.2, C6.2, J1.6, J1.9, J1.14, J1.20, J1.25, J1.30, J1.34, J1.39, U1.1 (A0), U1.2 (A1), U1.3 (A2), U1.4 (VSS), U2.9 (EM4), U2.11 (EM3), U2.13 (EM2), U2.15 (EM1), U3.2, U3.4, U4.2, U5.3, U7.4 (GND1), U9.9 (EM4), U9.11 (EM3), U9.13 (EM2), U9.15 (EM1), U10.2, U10.4, U11.2, U12.3
unnamed: D29.2 (A), F1.2
unnamed: D32.1 (K), R36.1
unnamed: F1.1, SW2.2
unnamed: R12.2, U3.1
unnamed: R13.2, U3.3
unnamed: R14.2, U4.1
unnamed: R15.2, U5.1
unnamed: R29.2, U10.1
unnamed: R30.2, U10.3
unnamed: R31.2, U11.1
unnamed: R32.2, U12.1
unnamed: H1.2, U1.7 (WP)
unnamed: R8.2, U2.1 (AN1)
unnamed: R6.2, U2.3 (AN2)
unnamed: R4.2, U2.5 (AN3)
unnamed: C4.1, R10.2, U2.7 (AN4)
unnamed: R25.2, U9.1 (AN1)
unnamed: R23.2, U9.3 (AN2)
unnamed: R21.2, U9.5 (AN3)
unnamed: R27.2, U9.7 (AN4)
unnamed: C11.1, U13.6 (VBST)
unnamed: R34.1, R35.1, U13.4 (VFB)
PI_SCL: J1.5, R17.2, U7.3 (SCL1)
PI_SDA: J1.3, R18.2, U7.2 (SDA1)
